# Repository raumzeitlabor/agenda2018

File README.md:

# agenda2018
Wir nehmen wieder teil an der Agenda Aktion der Stadt Mannheim. Diesmal ist der Bausatz den wir mit den Kindern löten wollen eine elektronische Okarina.

## Toolchain
### 3d models
OpenScad, Slicer(Cura)
Use non-toxic pla
### hardware
kiCad
### Software
Arduino IDE with Atmel AVR board definitions

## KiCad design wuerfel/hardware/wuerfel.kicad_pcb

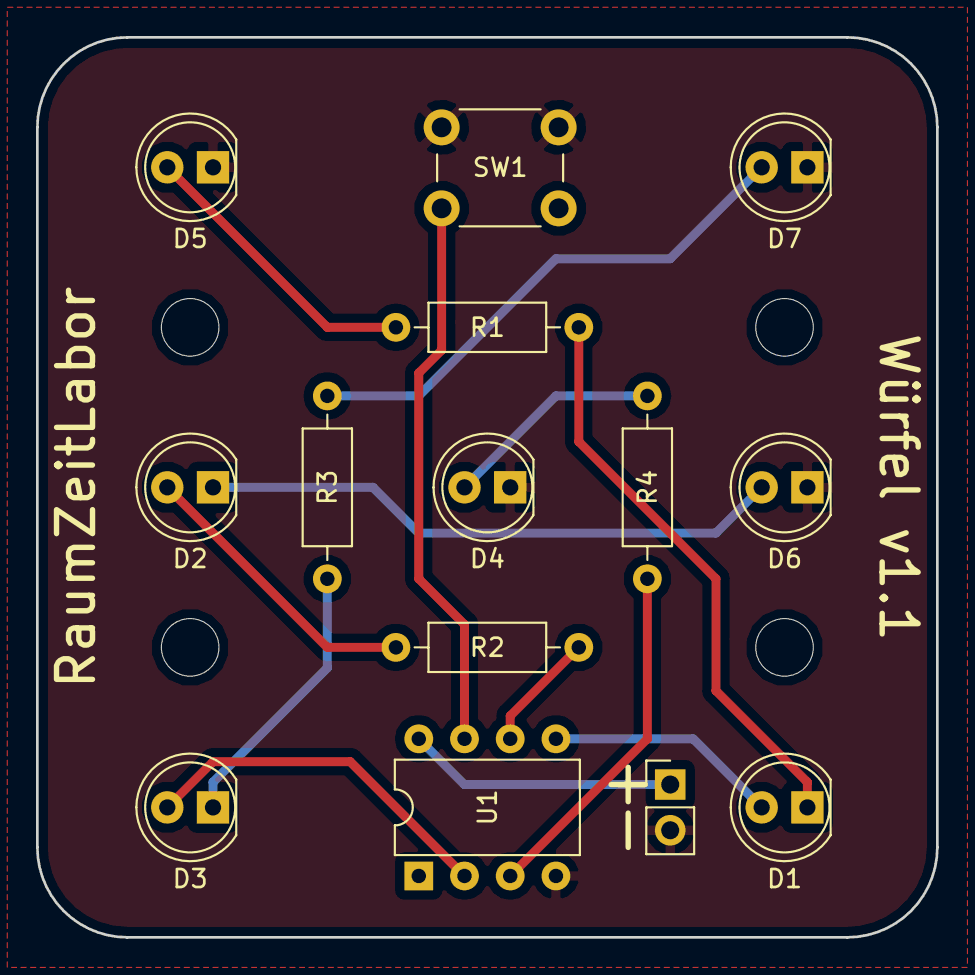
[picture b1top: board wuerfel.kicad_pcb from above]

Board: 2 copper layers, 50.0 x 50.0 mm, 14 parts (0 on the bottom side), 14 nets.

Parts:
BT1: Battery; PinHeader_1x02_P2.54mm_Vertical
D1, D2, D3, D4, D5, D6, D7: LED; LED_D5.0mm
R1, R2, R3, R4: R; R_Axial_DIN0207_L6.3mm_D2.5mm_P10.16mm_Horizontal
SW1: SW_Push; SW_PUSH_6mm
U1: ATTINY85-20PU; DIP-8_W7.62mm

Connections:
GND: BT1.2, D4.1, D5.1, D6.1, D7.1, SW1.1, U1.4
unnamed: D1.1, R1.1
unnamed: D1.2, U1.5
unnamed: D2.1, D6.2
unnamed: D2.2, R2.2
unnamed: D3.1, R3.1
unnamed: D3.2, U1.2
unnamed: D4.2, R4.2
unnamed: D5.2, R1.2
unnamed: D7.2, R3.2
unnamed: R2.1, U1.6
unnamed: R4.1, U1.3
unnamed: SW1.2, U1.7
VCC: BT1.1, U1.8

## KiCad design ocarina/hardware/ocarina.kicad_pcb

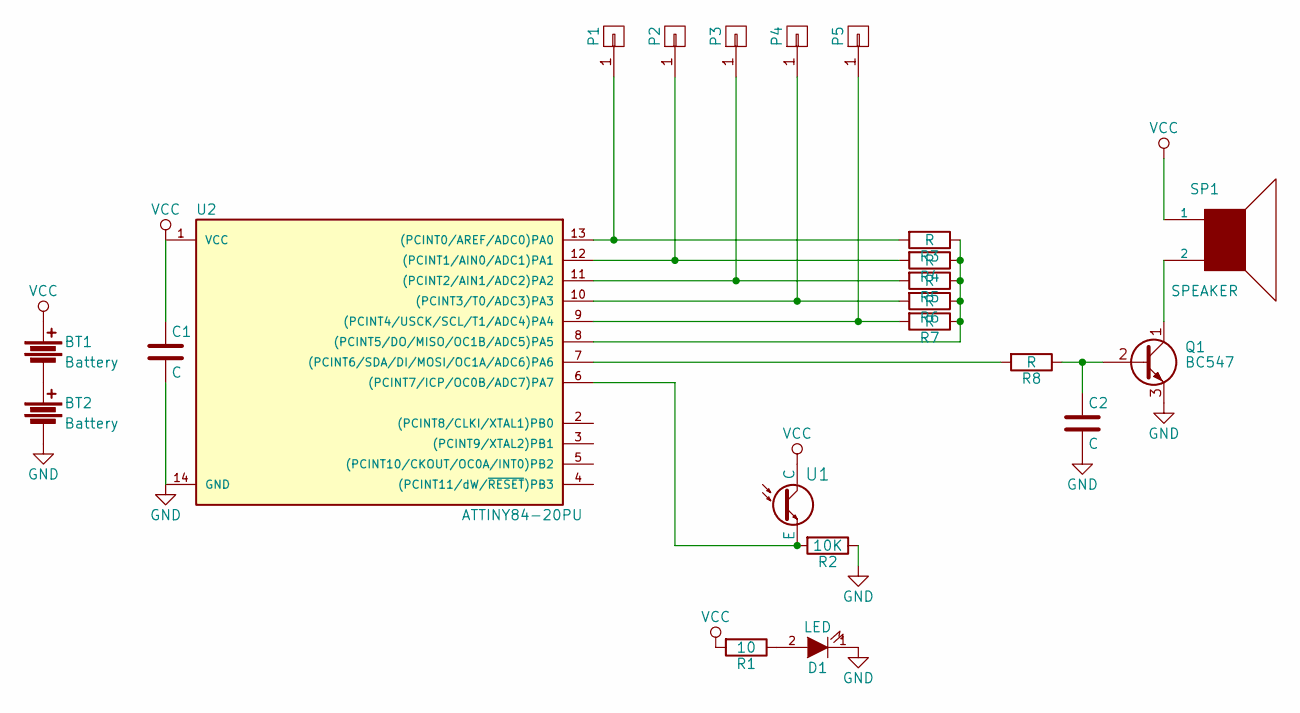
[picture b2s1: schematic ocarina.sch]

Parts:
BT1, BT2: Battery; batteryholder_AAA_BC0401
C1, C2: C; C_Disc_D5.0mm_W2.5mm_P2.50mm
D1: LED; LED-3MM
P1, P2, P3, P4, P5: CONN_01X01; MountingHole_3.2mm_M3_Pad
Q1: BC547; TO-92_Molded_Narrow
R1: 10; Resistor_Horizontal_RM10mm
R2: 10K; Resistor_Horizontal_RM10mm
R3, R4, R5, R6, R7, R8: R; Resistor_Horizontal_RM10mm
SP1: SPEAKER; CP_Radial_D24.0mm_P10.00mm_SnapIn
U1: Phototransistor; LED-5MM
U2: ATTINY84-20PU; DIP-14_W7.62mm

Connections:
GND: BT2.2, C1.2, C2.2, D1.1 (K), Q1.3 (E), R2.1, U2.14 (GND)
unnamed: BT1.2, BT2.1
unnamed: C2.1, Q1.2 (B), R8.1
unnamed: D1.2 (A), R1.1
unnamed: P1.1, R3.2, U2.13 ((PCINT0/AREF/ADC0)PA0)
unnamed: P2.1, R4.2, U2.12 ((PCINT1/AIN0/ADC1)PA1)
unnamed: P3.1, R5.2, U2.11 ((PCINT2/AIN1/ADC2)PA2)
unnamed: P4.1, R6.2, U2.10 ((PCINT3/T0/ADC3)PA3)
unnamed: P5.1, R7.2, U2.9 ((PCINT4/USCK/SCL/T1/ADC4)PA4)
unnamed: Q1.1 (C), SP1.2
unnamed: R2.2, U1.2 (E), U2.6 ((PCINT7/ICP/OC0B/ADC7)PA7)
unnamed: R3.1, R4.1, R5.1, R6.1, R7.1, U2.8 ((PCINT5/DO/MISO/OC1B/ADC5)PA5)
unnamed: R8.2, U2.7 ((PCINT6/SDA/DI/MOSI/OC1A/ADC6)PA6)
VCC: BT1.1, C1.1, R1.2, SP1.1, U1.1 (C), U2.1 (VCC)

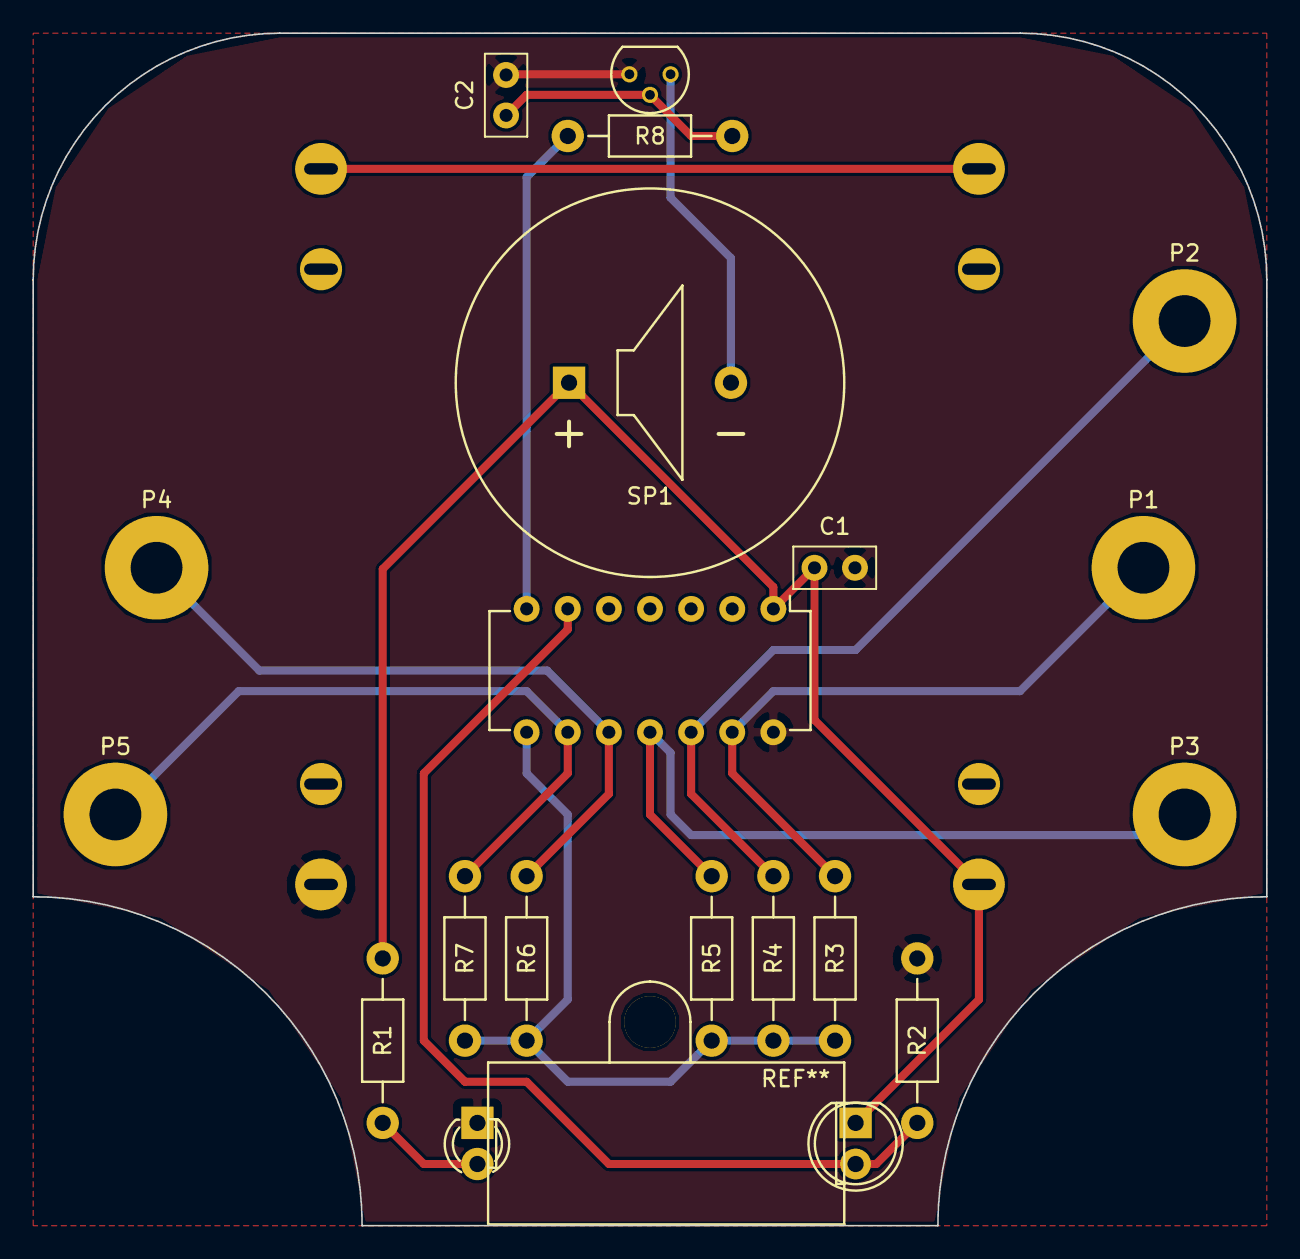
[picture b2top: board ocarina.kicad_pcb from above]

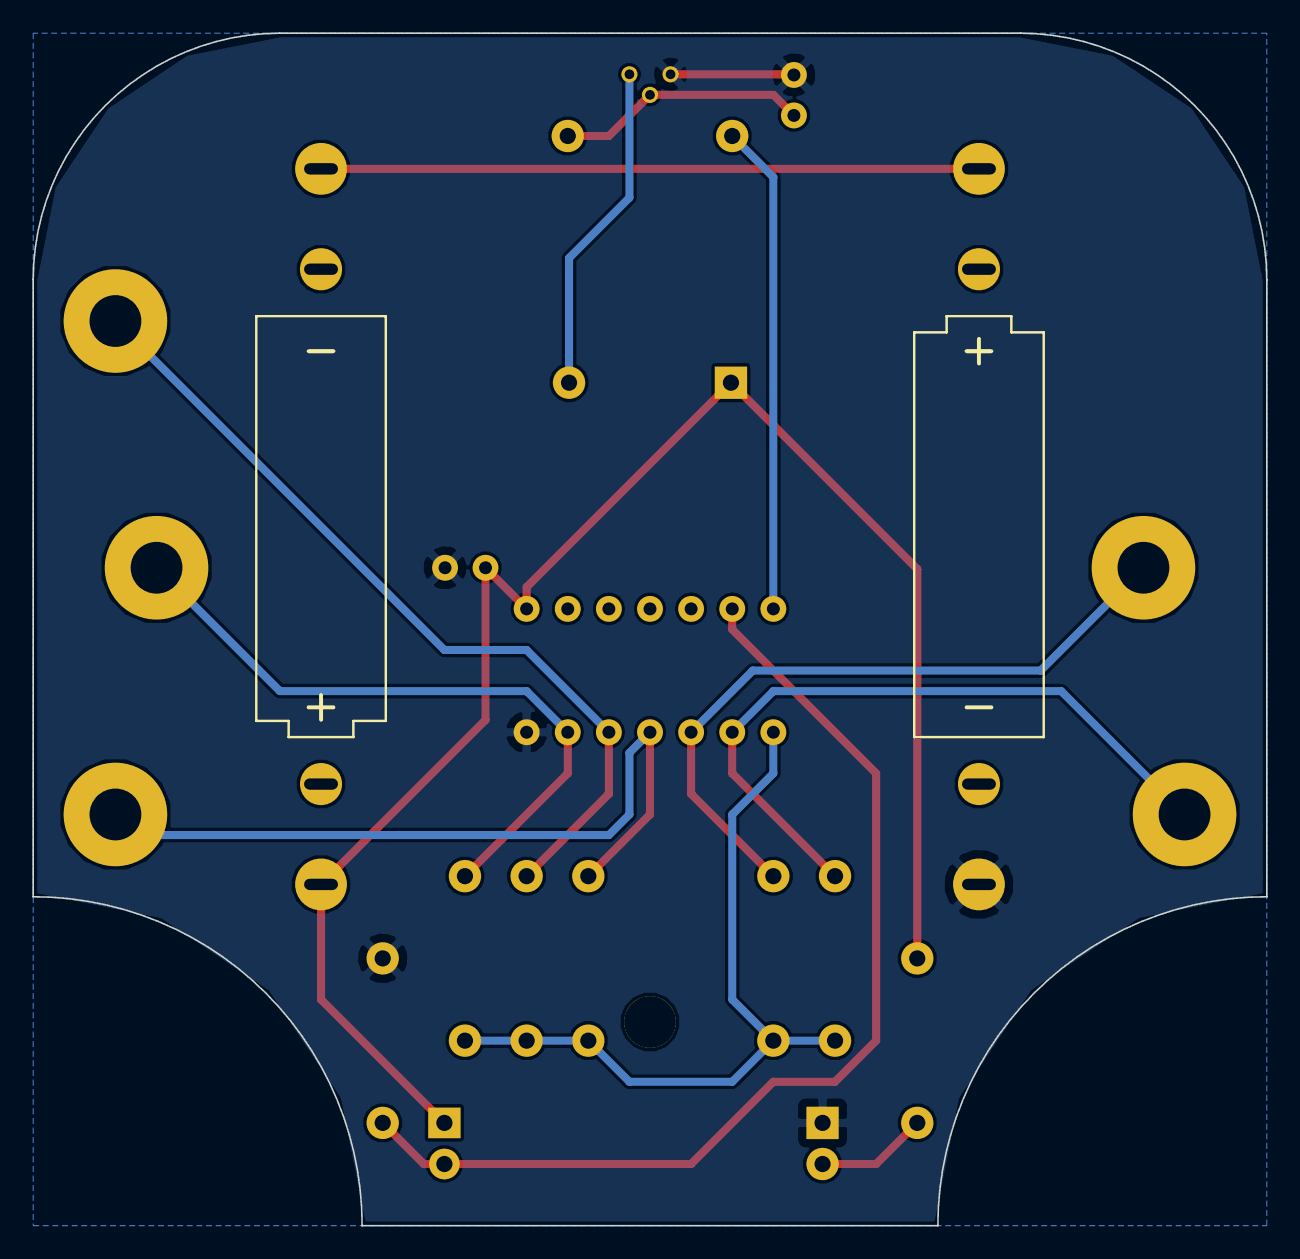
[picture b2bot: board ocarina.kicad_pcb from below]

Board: 2 copper layers, 76.2 x 73.7 mm, 22 parts (2 on the bottom side), 14 nets.

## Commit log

2018-03-02 Add 3d model
2018-05-13 Add kicad pcb schematics
2018-07-10 Add new project Wuerfel
